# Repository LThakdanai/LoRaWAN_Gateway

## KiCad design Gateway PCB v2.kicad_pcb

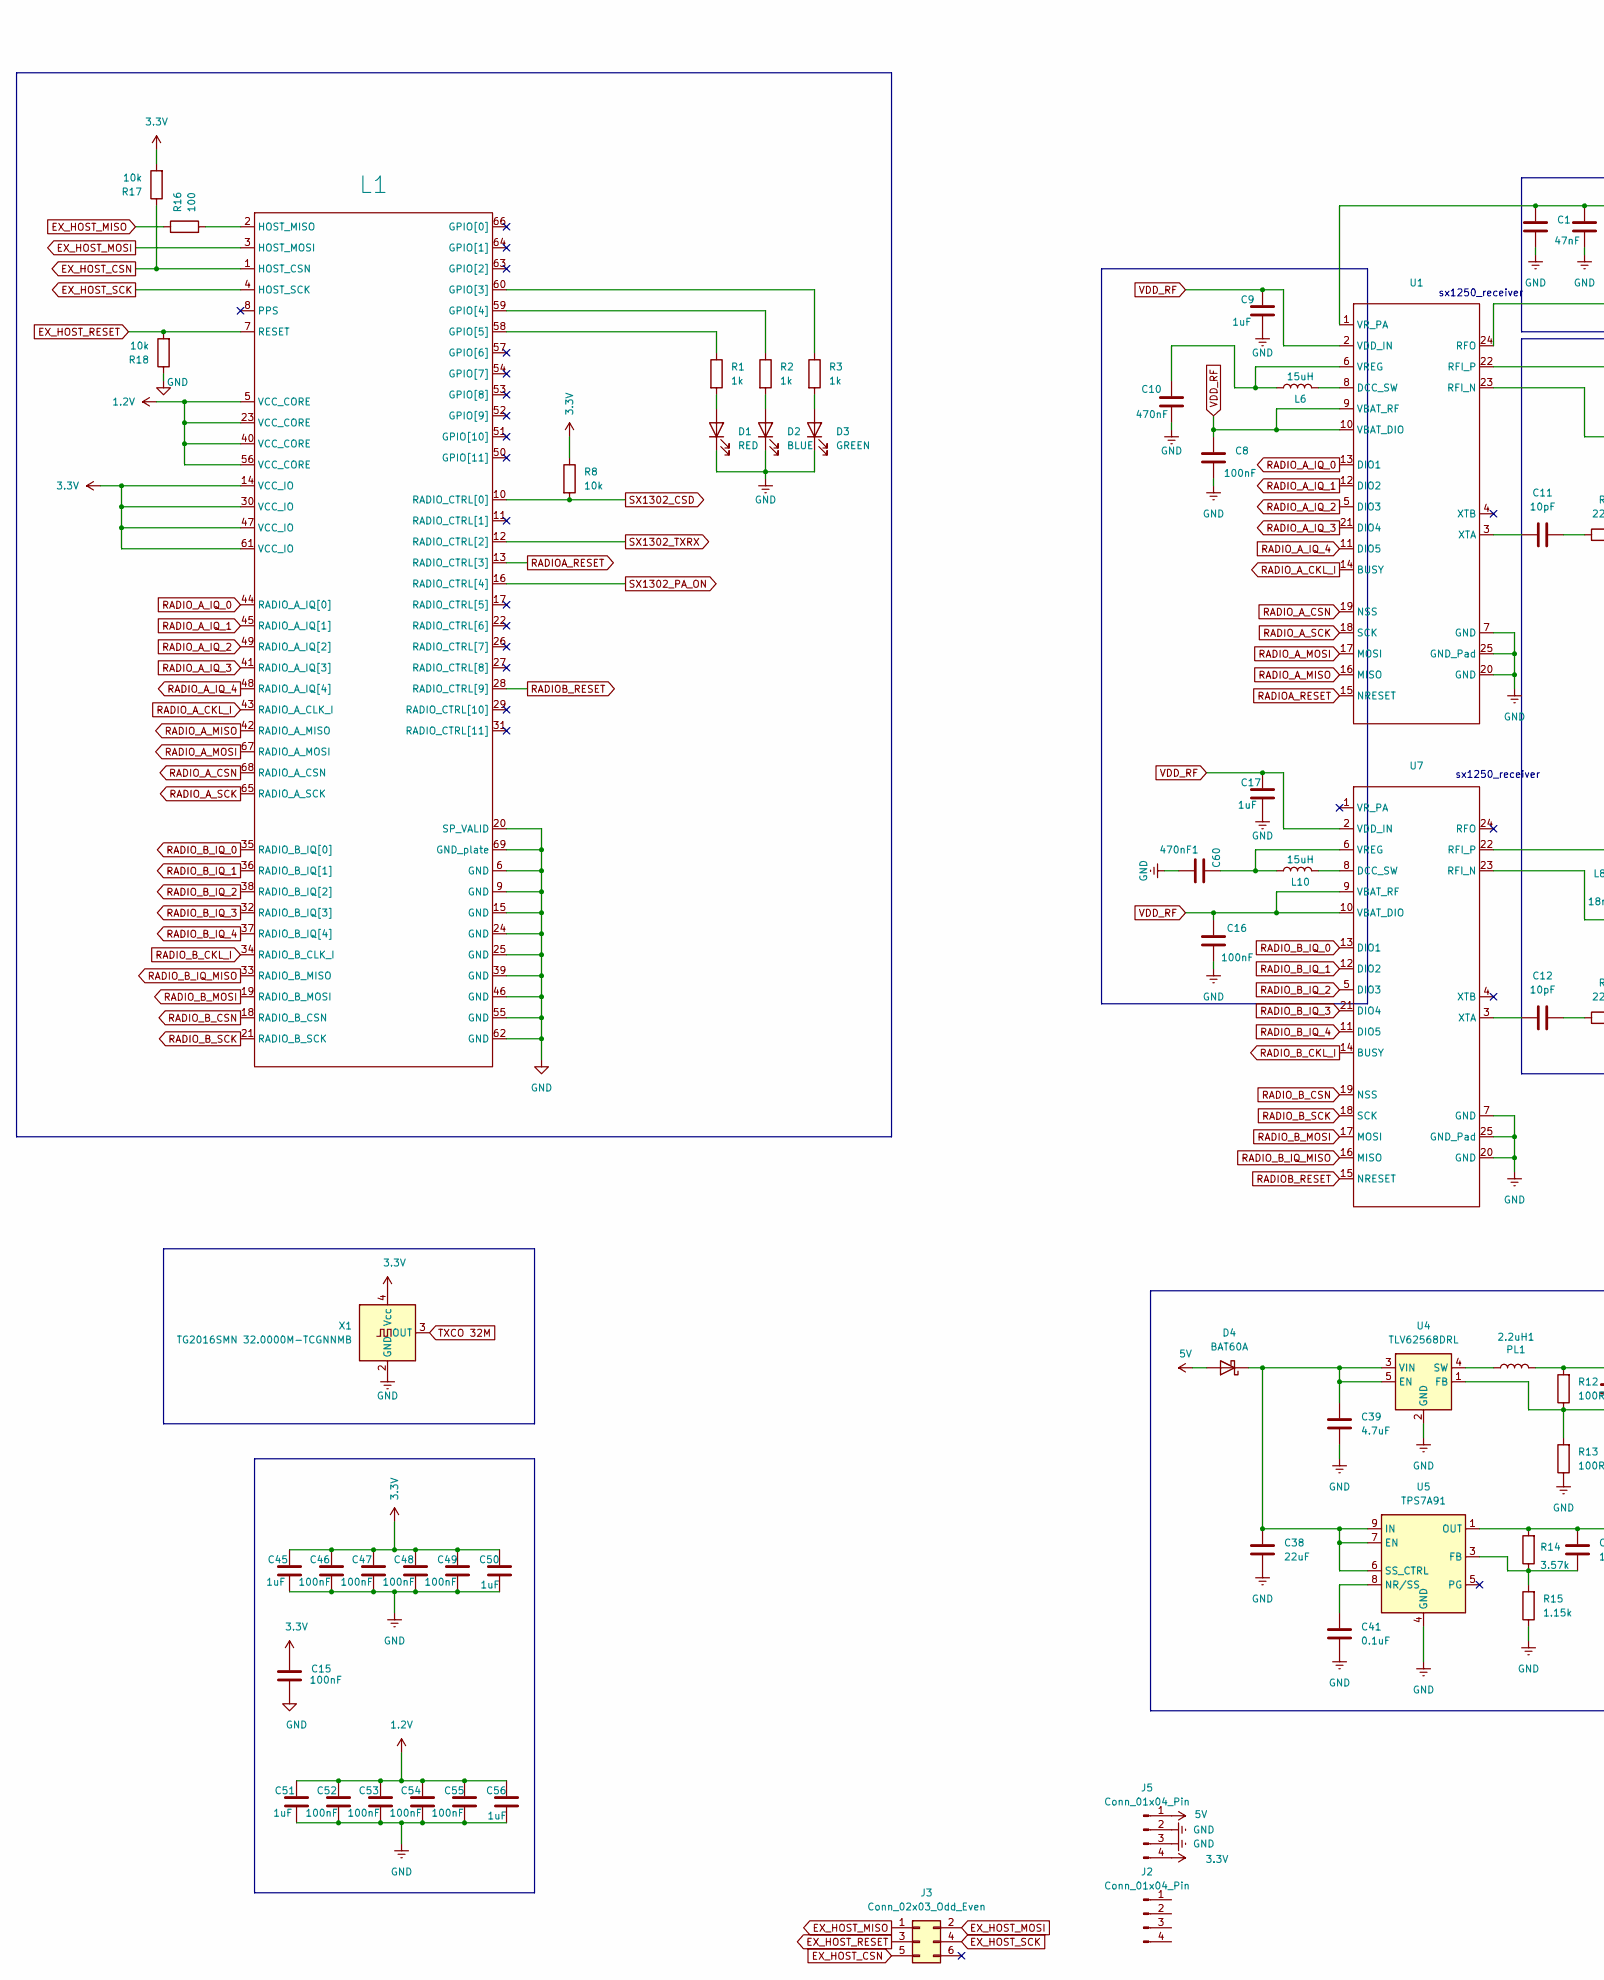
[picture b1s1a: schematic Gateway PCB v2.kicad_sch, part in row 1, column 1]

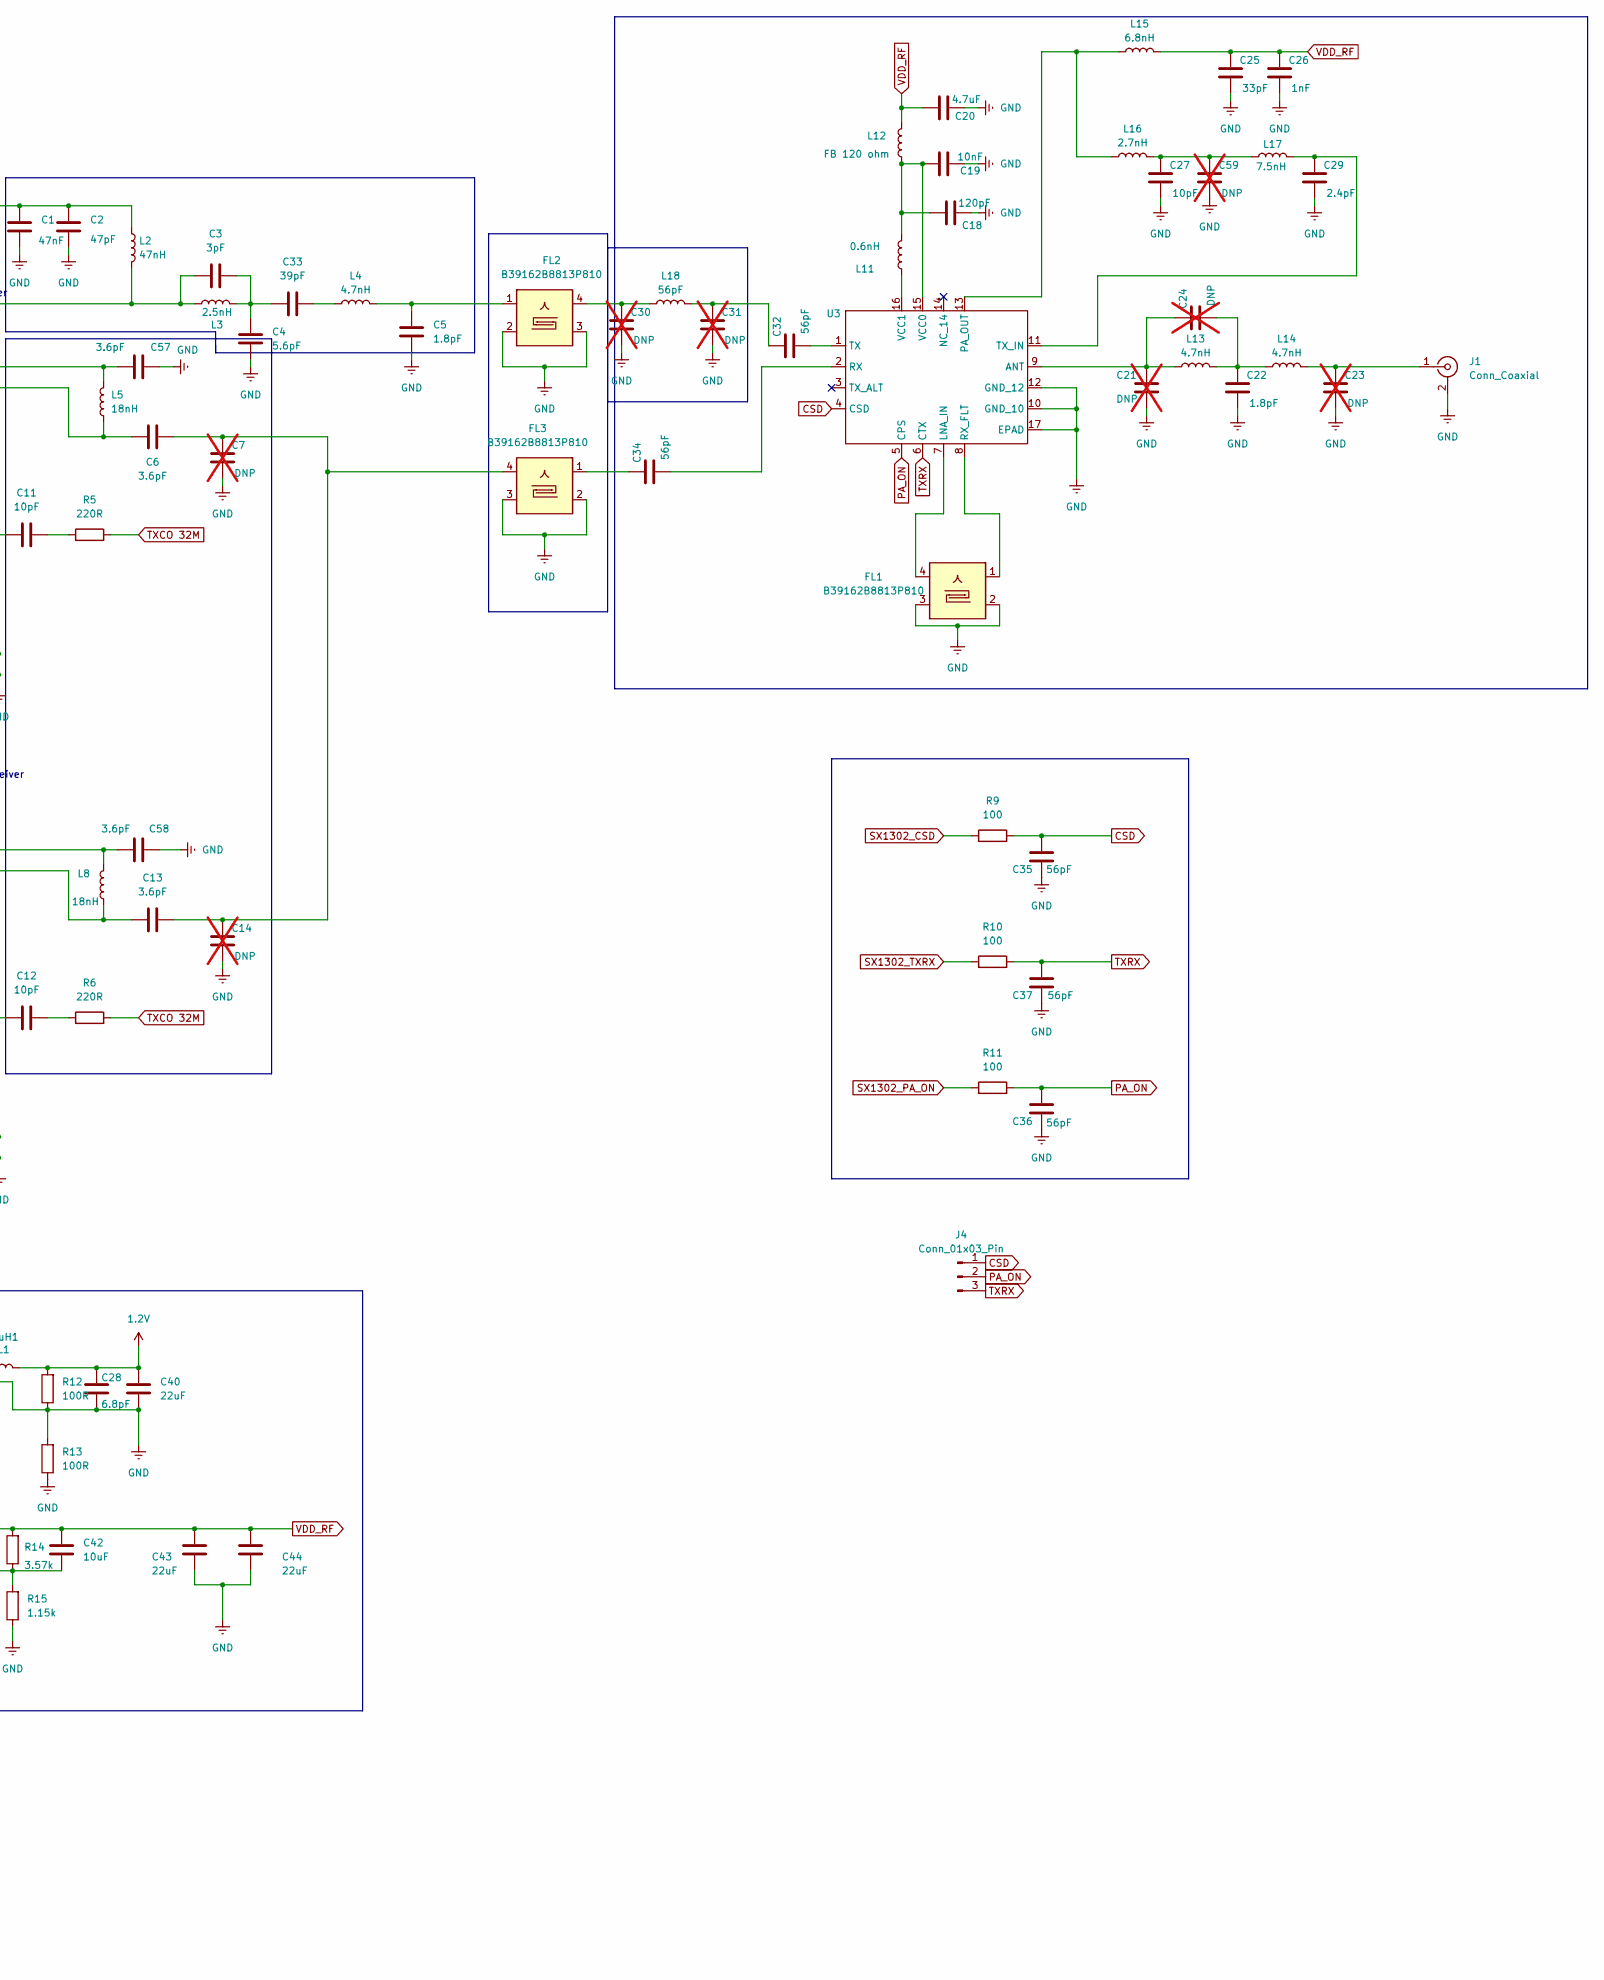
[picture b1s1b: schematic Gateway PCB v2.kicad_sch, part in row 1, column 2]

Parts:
C1: 47nF; C_0402_1005Metric_Pad0.74x0.62mm_HandSolder
C2: 47pF; C_0402_1005Metric_Pad0.74x0.62mm_HandSolder
C3: 3pF; C_0402_1005Metric_Pad0.74x0.62mm_HandSolder
C4: 5.6pF; C_0402_1005Metric_Pad0.74x0.62mm_HandSolder
C5, C22: 1.8pF; C_0402_1005Metric_Pad0.74x0.62mm_HandSolder
C6, C13, C57, C58: 3.6pF; C_0402_1005Metric_Pad0.74x0.62mm_HandSolder
C7, C14, C21, C23, C24, C30, C31, C59: DNP; C_0402_1005Metric_Pad0.74x0.62mm_HandSolder; not fitted
C8, C15, C16, C46, C47, C48, C49, C52, C53, C54, C55: 100nF; C_0402_1005Metric_Pad0.74x0.62mm_HandSolder
C9, C17, C45, C50, C51, C56: 1uF; C_0402_1005Metric_Pad0.74x0.62mm_HandSolder
C10: 470nF; C_0402_1005Metric_Pad0.74x0.62mm_HandSolder
C11, C12, C27: 10pF; C_0402_1005Metric_Pad0.74x0.62mm_HandSolder
C18: 120pF; C_0402_1005Metric_Pad0.74x0.62mm_HandSolder
C19: 10nF; C_0402_1005Metric_Pad0.74x0.62mm_HandSolder
C20, C39: 4.7uF; C_0402_1005Metric_Pad0.74x0.62mm_HandSolder
C25: 33pF; C_0402_1005Metric_Pad0.74x0.62mm_HandSolder
C26: 1nF; C_0402_1005Metric_Pad0.74x0.62mm_HandSolder
C28: 6.8pF; C_0402_1005Metric_Pad0.74x0.62mm_HandSolder
C29: 2.4pF; C_0402_1005Metric_Pad0.74x0.62mm_HandSolder
C32, C34, C35, C36, C37: 56pF; C_0402_1005Metric_Pad0.74x0.62mm_HandSolder
C33: 39pF; C_0402_1005Metric_Pad0.74x0.62mm_HandSolder
C38: 22uF; C_0603_1608Metric_Pad1.08x0.95mm_HandSolder
C40, C43, C44: 22uF; C_0402_1005Metric_Pad0.74x0.62mm_HandSolder
C41: 0.1uF; C_0402_1005Metric_Pad0.74x0.62mm_HandSolder
C42: 10uF; C_0402_1005Metric_Pad0.74x0.62mm_HandSolder
C60: 470nF1; C_0402_1005Metric_Pad0.74x0.62mm_HandSolder
D1: RED; LED_0603_1608Metric_Pad1.05x0.95mm_HandSolder
D2: BLUE; LED_0603_1608Metric_Pad1.05x0.95mm_HandSolder
D3: GREEN; LED_0603_1608Metric_Pad1.05x0.95mm_HandSolder
D4: BAT60A; D_SOD-323
FL1, FL2, FL3: B39162B8813P810; Filter_1109-5_1.1x0.9mm
J1: Conn_Coaxial; SMA_BAT_Wireless_BWSMA-KWE-Z001
J2: Conn_01x04_Pin; PinSocket_1x04_P2.54mm_Vertical
J3: Conn_02x03_Odd_Even; PinHeader_2x03_P2.54mm_Vertical
J4: Conn_01x03_Pin; PinHeader_1x03_P2.54mm_Vertical
J5: Conn_01x04_Pin
L1: SX1302
L2: 47nH; L_0402_1005Metric_Pad0.77x0.64mm_HandSolder
L3: 2.5nH; L_0402_1005Metric_Pad0.77x0.64mm_HandSolder
L4, L13, L14: 4.7nH; L_0402_1005Metric_Pad0.77x0.64mm_HandSolder
L5, L8: 18nH; L_0402_1005Metric_Pad0.77x0.64mm_HandSolder
L6, L10: 15uH; L_0805_2012Metric_Pad1.05x1.20mm_HandSolder
L11: 0.6nH; L_0402_1005Metric_Pad0.77x0.64mm_HandSolder
L12: FB 120 ohm; L_0402_1005Metric
L15: 6.8nH; L_0402_1005Metric_Pad0.77x0.64mm_HandSolder
L16: 2.7nH; L_0402_1005Metric_Pad0.77x0.64mm_HandSolder
L17: 7.5nH; L_0402_1005Metric_Pad0.77x0.64mm_HandSolder
L18: 56pF; L_0402_1005Metric_Pad0.77x0.64mm_HandSolder
PL1: 2.2uH1; L_1008_2520Metric_Pad1.43x2.20mm_HandSolder
R1, R2, R3: 1k; R_0402_1005Metric_Pad0.72x0.64mm_HandSolder
R5, R6: 220R; R_0402_1005Metric_Pad0.72x0.64mm_HandSolder
R8, R17, R18: 10k; R_0402_1005Metric_Pad0.72x0.64mm_HandSolder
R9, R10, R11, R16: 100; R_0402_1005Metric_Pad0.72x0.64mm_HandSolder
R12, R13: 100R; R_0402_1005Metric_Pad0.72x0.64mm_HandSolder
R14: 3.57k; R_0402_1005Metric_Pad0.72x0.64mm_HandSolder
R15: 1.15k; R_0402_1005Metric_Pad0.72x0.64mm_HandSolder
U1, U7: HVQFN-24-1EP_4x4mm_P0.5mm_EP2.5x2.5mm
U3: QFN-16-1EP_3x3mm_P0.5mm_EP1.75x1.75mm
U4: TLV62568DRL; SOT-563
U5: TPS7A91; Texas_S-PDSO-N10_EP1.2x2mm
X1: TG2016SMN 32.0000M-TCGNNMB; Oscillator_SMD_SeikoEpson_TG2520SMN-xxx-xxxxxx-4Pin_2.5x2.0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

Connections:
1.2V: C28.1, C40.2, C51.1, C52.1, C53.1, C54.1, C55.1, C56.1, L1.5 (VCC_CORE), L1.23 (VCC_CORE), L1.40 (VCC_CORE), L1.56 (VCC_CORE), PL1.2, R12.2
3.3V: C15.1, C45.1, C46.1, C47.1, C48.1, C49.1, C50.1, J2.4, J5.4, L1.14 (VCC_IO), L1.30 (VCC_IO), L1.47 (VCC_IO), L1.61 (VCC_IO), R8.1, R17.2, X1.4 (Vcc)
5V: D4.2 (A), J2.1, J5.1
CSD: C35.2, J4.1, R9.2, U3.4 (CSD)
EX_HOST_CSN: J3.5, L1.1 (HOST_CSN), R17.1
EX_HOST_MISO: J3.1, R16.1
EX_HOST_MOSI: J3.2, L1.3 (HOST_MOSI)
EX_HOST_RESET: J3.3, L1.7 (RESET), R18.2
EX_HOST_SCK: J3.4, L1.4 (HOST_SCK)
GND: C1.2, C2.2, C4.2, C5.2, C7.2, C8.2, C9.2, C10.2, C14.2, C15.2, C16.2, C17.2, C18.2, C19.2, C20.2, C21.2, C22.2, C23.2, C25.2, C26.2, C27.2, C28.2, C29.2, C30.2, C31.2, C35.1, C36.1, C37.1, C38.1, C39.1, C40.1, C41.1, C43.1, C44.1, C45.2, C46.2, C47.2, C48.2, C49.2, C50.2, C51.2, C52.2, C53.2, C54.2, C55.2, C56.2, C57.1, C58.1, C59.2, C60.2, D1.1 (K), D2.1 (K), D3.1 (K), FL1.2, FL1.3, FL1.5, FL2.2, FL2.3, FL2.5, FL3.2, FL3.3, FL3.5, J1.2 (Ext), J2.2, J2.3, J5.2, J5.3, L1.6 (GND), L1.9 (GND), L1.15 (GND), L1.20 (SP_VALID), L1.24 (GND), L1.25 (GND), L1.39 (GND), L1.46 (GND), L1.55 (GND), L1.62 (GND), L1.69 (GND_plate), R12.1, R13.1, R13.2, R15.1, R18.1, U1.7 (GND), U1.20 (GND), U1.25 (GND_Pad), U3.10 (GND_10), U3.12 (GND_12), U3.17 (EPAD), U4.1 (FB), U4.2 (GND), U5.4 (GND), U5.11 (GND), U7.7 (GND), U7.20 (GND), U7.25 (GND_Pad), X1.2 (GND)
unnamed: C3.2, C4.1, C33.1, L3.2
unnamed: C5.1, FL2.1, L4.2
unnamed: C11.2, R5.1
unnamed: C12.2, R6.1
unnamed: C6.2, C7.1, C13.2, C14.1, FL3.4
unnamed: C22.1, C24.2, L13.2, L14.1
unnamed: C27.1, C59.1, L16.2, L17.1
unnamed: C30.1, FL2.4, L18.1
unnamed: C31.1, C32.1, L18.2
unnamed: C33.2, L4.1
unnamed: C34.1, FL3.1
unnamed: D1.2 (A), R1.2
unnamed: D2.2 (A), R2.2
unnamed: D3.2 (A), R3.2
unnamed: C38.2, C39.2, D4.1 (K), U4.3 (VIN), U4.5 (EN), U5.6 (SS_CTRL), U5.7 (EN), U5.9 (IN), U5.10 (IN)
unnamed: C23.1, J1.1 (In), L14.2
unnamed: L1.60 (GPIO[3]), R3.1
unnamed: L1.59 (GPIO[4]), R2.1
unnamed: L1.58 (GPIO[5]), R1.1
unnamed: L1.2 (HOST_MISO), R16.2
unnamed: L6.2, U1.8 (DCC_SW)
unnamed: C6.1, L5.1, U1.23 (RFI_N)
unnamed: C57.2, L5.2, U1.22 (RFI_P)
unnamed: C3.1, L2.2, L3.1, U1.24 (RFO)
unnamed: C10.1, L6.1, U1.6 (VREG)
unnamed: C1.1, C2.1, L2.1, U1.1 (VR_PA)
unnamed: C11.1, U1.3 (XTA)
unnamed: C21.1, C24.1, L13.1, U3.9 (ANT)
unnamed: FL1.4, U3.7 (LNA_IN)
unnamed: L15.1, L16.1, U3.13 (PA_OUT)
unnamed: C34.2, U3.2 (RX)
unnamed: FL1.1, U3.8 (RX_FLT)
unnamed: C32.2, U3.1 (TX)
unnamed: C29.1, L17.2, U3.11 (TX_IN)
unnamed: C18.1, C19.1, L11.2, L12.1, U3.15 (VCC0)
unnamed: L11.1, U3.16 (VCC1)
unnamed: PL1.1, U4.4 (SW)
unnamed: C42.1, R14.1, R15.2, U5.3 (FB)
unnamed: C41.2, U5.8 (NR/SS)
unnamed: L10.2, U7.8 (DCC_SW)
unnamed: C13.1, L8.1, U7.23 (RFI_N)
unnamed: C58.2, L8.2, U7.22 (RFI_P)
unnamed: C60.1, L10.1, U7.6 (VREG)
unnamed: C12.1, U7.3 (XTA)
PA_ON: C36.2, J4.2, R11.2, U3.5 (CPS)
RADIOA_RESET: L1.13 (RADIO_CTRL[3]), U1.15 (NRESET)
RADIOB_RESET: L1.28 (RADIO_CTRL[9]), U7.15 (NRESET)
RADIO_A_CKL_I: L1.43 (RADIO_A_CLK_I), U1.14 (BUSY)
RADIO_A_CSN: L1.68 (RADIO_A_CSN), U1.19 (NSS)
RADIO_A_IQ_0: L1.44 (RADIO_A_IQ[0]), U1.13 (DIO1)
RADIO_A_IQ_1: L1.45 (RADIO_A_IQ[1]), U1.12 (DIO2)
RADIO_A_IQ_2: L1.49 (RADIO_A_IQ[2]), U1.5 (DIO3)
RADIO_A_IQ_3: L1.41 (RADIO_A_IQ[3]), U1.21 (DIO4)
RADIO_A_IQ_4: L1.48 (RADIO_A_IQ[4]), U1.11 (DIO5)
RADIO_A_MISO: L1.42 (RADIO_A_MISO), U1.16 (MISO)
RADIO_A_MOSI: L1.67 (RADIO_A_MOSI), U1.17 (MOSI)
RADIO_A_SCK: L1.65 (RADIO_A_SCK), U1.18 (SCK)
RADIO_B_CKL_I: L1.34 (RADIO_B_CLK_I), U7.14 (BUSY)
RADIO_B_CSN: L1.18 (RADIO_B_CSN), U7.19 (NSS)
RADIO_B_IQ_0: L1.35 (RADIO_B_IQ[0]), U7.13 (DIO1)
RADIO_B_IQ_1: L1.36 (RADIO_B_IQ[1]), U7.12 (DIO2)
RADIO_B_IQ_2: L1.38 (RADIO_B_IQ[2]), U7.5 (DIO3)
RADIO_B_IQ_3: L1.32 (RADIO_B_IQ[3]), U7.21 (DIO4)
RADIO_B_IQ_4: L1.37 (RADIO_B_IQ[4]), U7.11 (DIO5)
RADIO_B_IQ_MISO: L1.33 (RADIO_B_MISO), U7.16 (MISO)
RADIO_B_MOSI: L1.19 (RADIO_B_MOSI), U7.17 (MOSI)
RADIO_B_SCK: L1.21 (RADIO_B_SCK), U7.18 (SCK)
SX1302_CSD: L1.10 (RADIO_CTRL[0]), R8.2, R9.1
SX1302_PA_ON: L1.16 (RADIO_CTRL[4]), R11.1
SX1302_TXRX: L1.12 (RADIO_CTRL[2]), R10.1
TXCO 32M: R5.2, R6.2, X1.3 (OUT)
TXRX: C37.2, J4.3, R10.2, U3.6 (CTX)
VDD_RF: C8.1, C9.1, C16.1, C17.1, C20.1, C25.1, C26.1, C42.2, C43.2, C44.2, L12.2, L15.2, R14.2, U1.2 (VDD_IN), U1.9 (VBAT_RF), U1.10 (VBAT_DIO), U5.1 (OUT), U5.2 (OUT), U7.2 (VDD_IN), U7.9 (VBAT_RF), U7.10 (VBAT_DIO)

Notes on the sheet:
sx1250_receiver

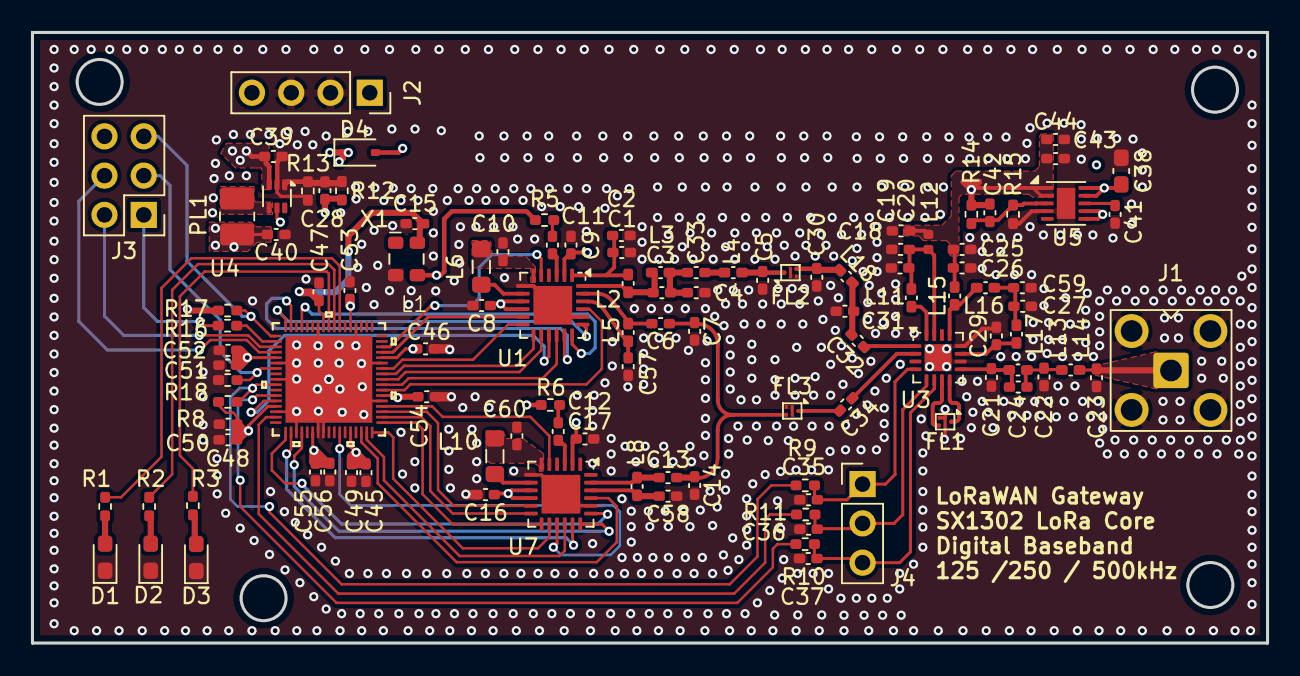
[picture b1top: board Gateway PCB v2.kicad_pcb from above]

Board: 4 copper layers, 79.9 x 39.5 mm, 110 parts (0 on the bottom side), 83 nets.

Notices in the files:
parts and their libraries:
Copyright 2016 Accelerated Designs. All rights reserved.
